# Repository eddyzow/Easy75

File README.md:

# Easy75

*because sometimes nine keys isn't enough...*

A custom 75% gasket-mounted mechanical keyboard run with a Raspberry Pi Pico. Features include 4.5-degree ergonomic incline, switch hotswap, 1.3" OLED screen, custom firmware, rotary encoder, custom printed circuit board (PCB), lubricated switches and stabilizers, and more! Created for Hack Club's Highway program.

[Easy75 Sound Test - Stock Akko V3 Creamy Blue Pro, Stock Durock V3](https://youtu.be/ZoHuPwVao3s)

# Gasket Mount

# PCB (designed and wired with KiCad)

# Case (designed in Onshape)

# Bill of Materials

| Item Name                                           | Purpose                                         | Item Source  | Quantity | Unit Cost (includes taxes) | Cost    | Notes                                                                 |
|:----------------------------------------------------|:------------------------------------------------|:-------------|---------:|:----------------------------|:--------|:----------------------------------------------------------------------|
| Akko V3 Creamy Blue Pro Switch (45pc)              | Mechanical switch for operating the keyboard    | Amazon       |        2 | $13.79                     | $27.58  |                                                                        |
| Pololu Laser-cut Switch Plate - 1.5mm Acrylic      | For switches to rest on and stability           | Pololu       |        1 | $31.00                     | $31.00  | Estimate -- precise cost is only available upon ordering               |
| 3D Printer Filament (PLA 1kg)                      | Print case (resin is too expensive)             | Bambu Lab    |        1 | $28.23                     | $28.23  |                                                                        |
| PCB x5 (min quantity)                              | Brains of the keyboard                          | JLCPCB       |        1 | $54.15                     | $54.15  | Could be $0 if PCBWay approves sponsorship                             |
| 1N4148 Diodes x100                                 | Prevents key ghosting                           | Amazon       |        1 | $5.73                      | $5.73   |                                                                        |
| Kailh Switch Sockets x50                           | Makes the board hotswap                         | Amazon       |        2 | $7.55                      | $15.10  |                                                                        |
| EC11 Rotary Encoder                                | Control for volume, etc in a knob               | AliExpress   |        1 | $6.11                      | $6.11   |                                                                        |
| Durock V3 Stabilizers                              | Stability for longer keys                       | Amazon       |        1 | $21.25                     | $21.25  |                                                                        |
| OLED Screen 128x64 1.3"                            | Provides a display for the keyboard             | Amazon       |        1 | $9.02                      | $9.02   |                                                                        |
| DIY Neoprene Gasket Strips                         | Creates a soft mount to improve sound quality   | Amazon       |        1 | $10.25                     | $10.25  |                                                                        |
| **TOTAL**                                          |                                                 |              |       12 |                            | **$225.66** |                                                                    |

For BOM with links, go to https://docs.google.com/spreadsheets/d/1KsEJJudN0m4QrFXq010_IyKu9P5RgScRp4gqEkQdcRI/edit?usp=sharing

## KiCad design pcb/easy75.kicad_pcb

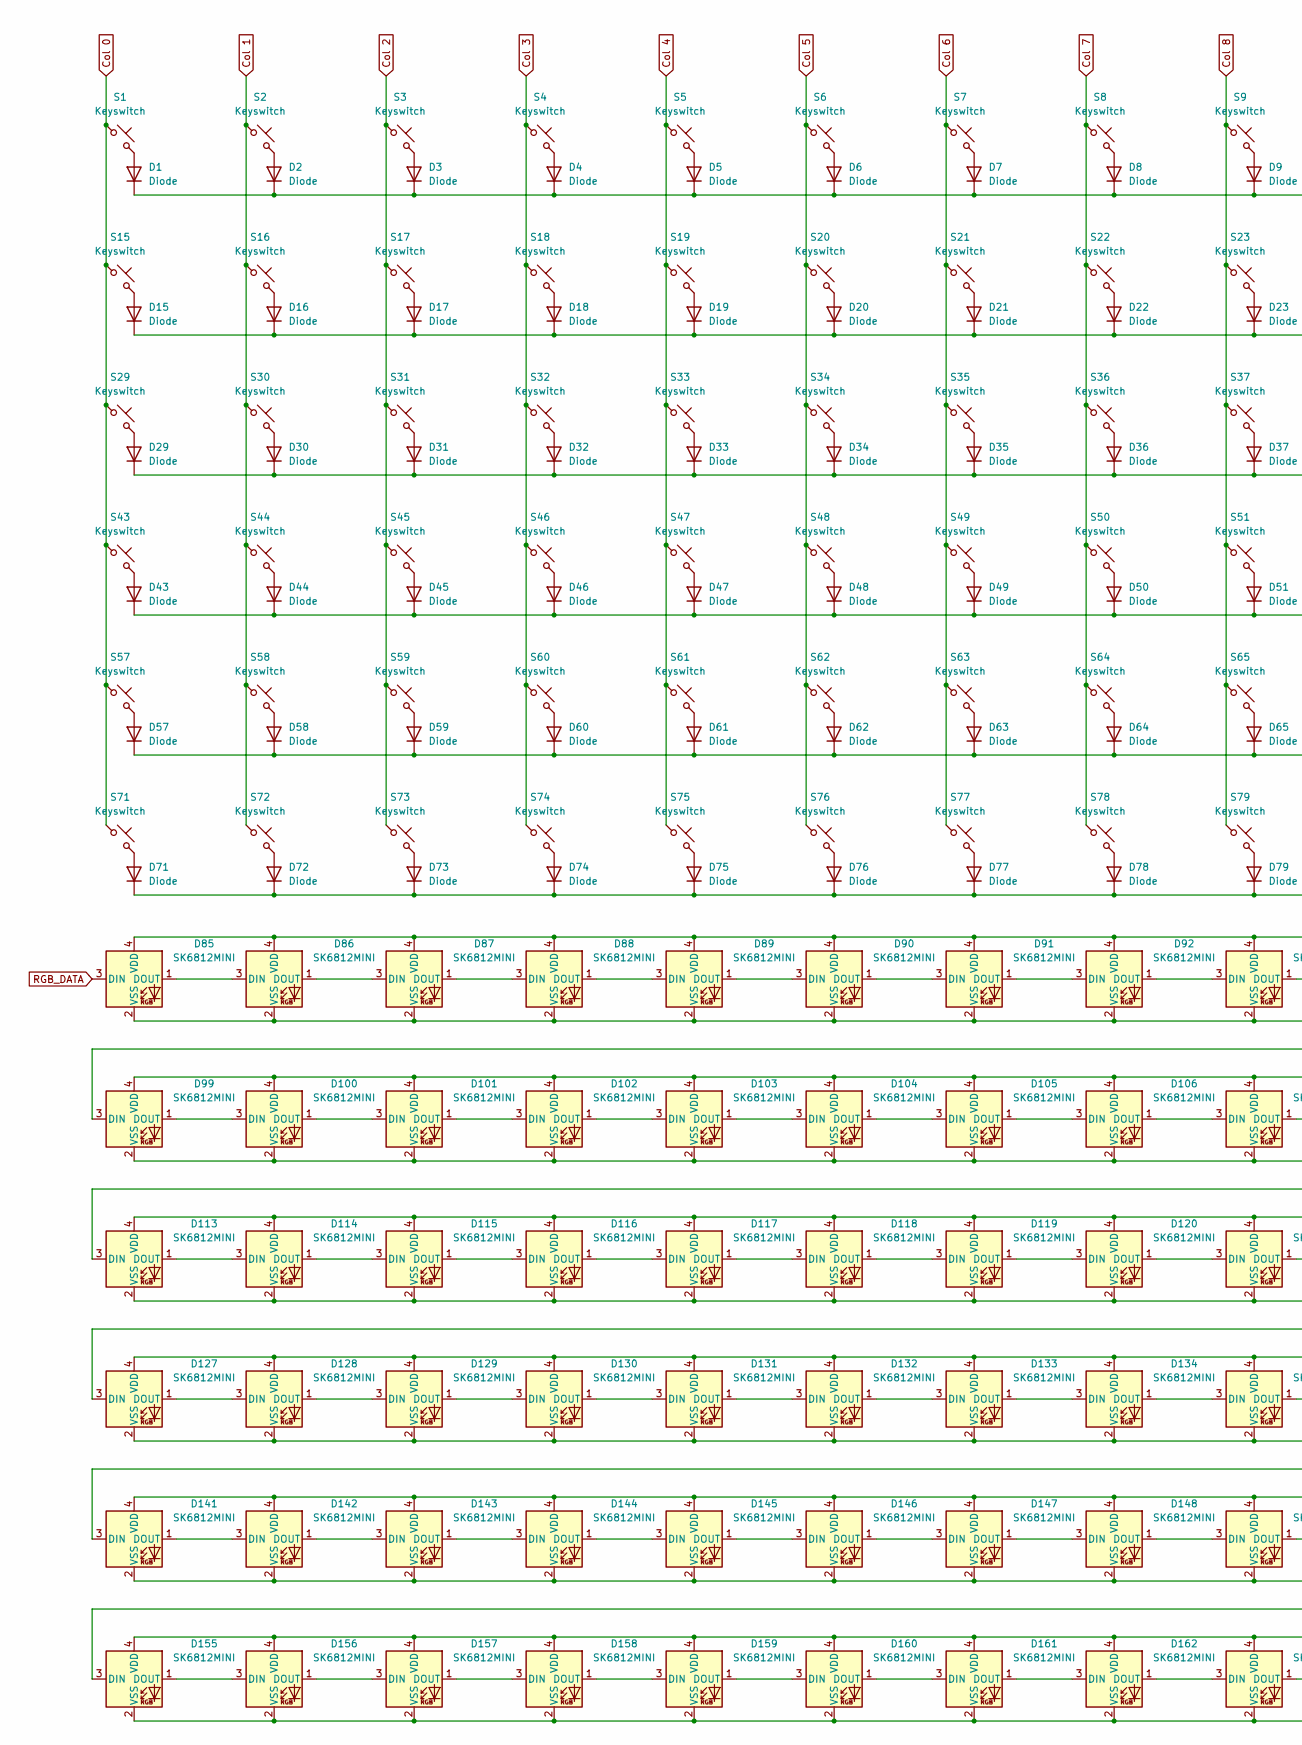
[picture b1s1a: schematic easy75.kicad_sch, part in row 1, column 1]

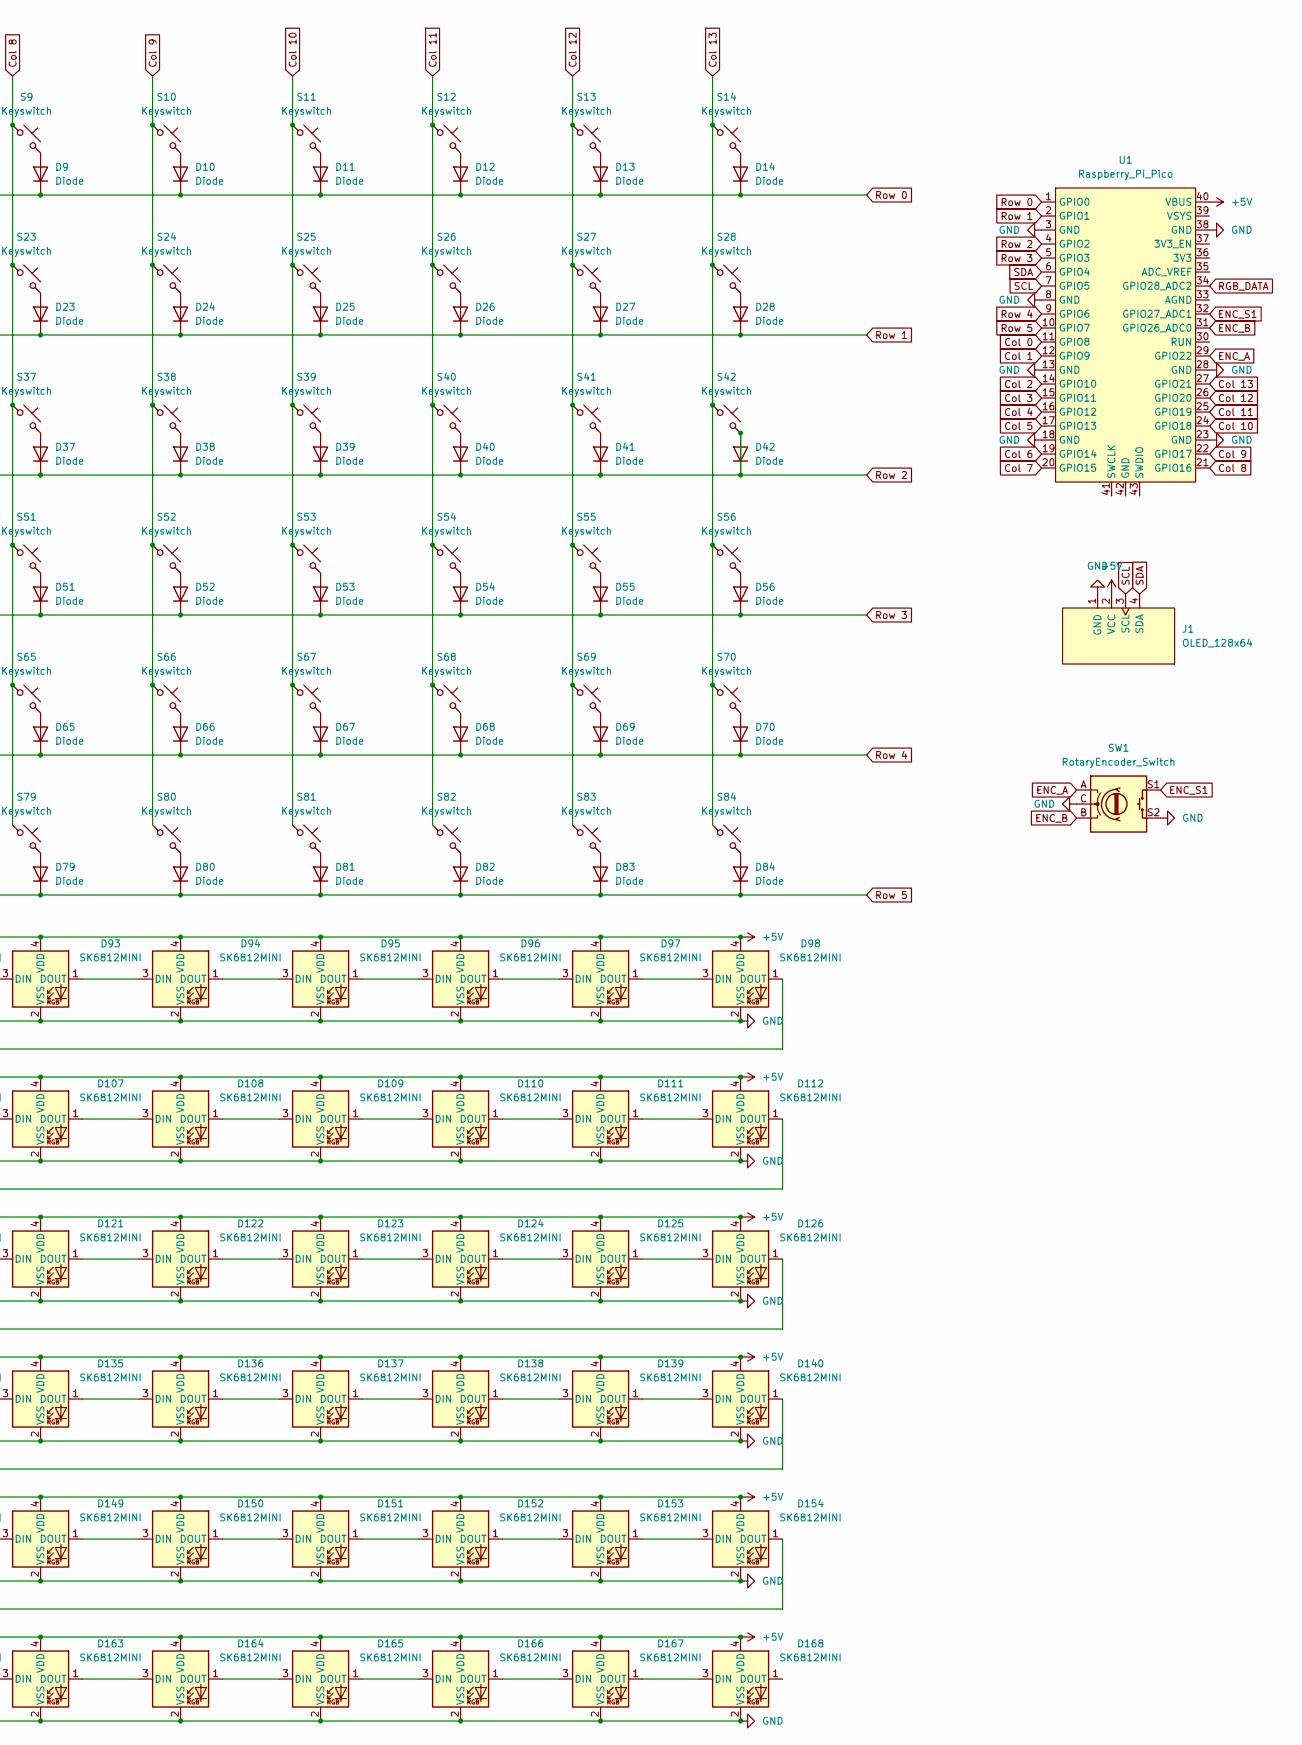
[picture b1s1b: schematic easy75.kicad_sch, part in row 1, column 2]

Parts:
D1, D2, D3, D4, D5, D6, D7, D8, D9, D10, D11, D12, D13, D14, D15, D16, D17, D18, D19, D20, D21, D22, D23, D24, D25, D26, D27, D28, D29, D30, D31, D32, D33, D34, D35, D36, D37, D38, D39, D40, D41, D42, D43, D44, D45, D46, D47, D48, D49, D50, D51, D52, D53, D54, D55, D56, D57, D58, D59, D60, D61, D62, D63, D64, D65, D66, D67, D68, D69, D70, D71, D72, D73, D74, D75, D76, D77, D78, D79, D80, D81, D82, D83, D84: Diode; Diode_DO-35
D85, D86, D87, D88, D89, D90, D91, D92, D93, D94, D95, D96, D97, D98, D99, D100, D101, D102, D103, D104, D105, D106, D107, D108, D109, D110, D111, D112, D113, D114, D115, D116, D117, D118, D119, D120, D121, D122, D123, D124, D125, D126, D127, D128, D129, D130, D131, D132, D133, D134, D135, D136, D137, D138, D139, D140, D141, D142, D143, D144, D145, D146, D147, D148, D149, D150, D151, D152, D153, D154, D155, D156, D157, D158, D159, D160, D161, D162, D163, D164, D165, D166, D167, D168: SK6812MINI; LED_SK6812MINI
J1: OLED_128x64
S1, S2, S3, S4, S5, S6, S7, S8, S9, S10, S11, S12, S13, S14, S15, S16, S17, S18, S19, S20, S21, S22, S23, S24, S25, S26, S27, S30, S31, S32, S33, S34, S35, S36, S37, S38, S39, S40, S41, S44, S45, S46, S47, S48, S49, S50, S51, S52, S53, S54, S57, S58, S59, S60, S61, S62, S63, S64, S65, S66, S68, S73, S74, S75, S76, S77, S78, S79, S80, S81, S82, S83, S84: Keyswitch; Hotswap_MX_1.00u
S28: Keyswitch; SW_Cherry_MX_2.00u_PCB
S29, S42: Keyswitch; Hotswap_MX_1.50u
S43, S67: Keyswitch; Hotswap_MX_1.75u
S55, S56: Keyswitch; SW_Cherry_MX_2.25u_PCB
S69, S70, S71: Keyswitch; Hotswap_MX_1.25u
S72: Keyswitch; Hotswap_MX_6.25u
SW1: RotaryEncoder_Switch; Encoder_EC11_MX
U1: Raspberry_Pi_Pico

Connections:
+5V: D85.4 (VDD), D86.4 (VDD), D87.4 (VDD), D88.4 (VDD), D89.4 (VDD), D90.4 (VDD), D91.4 (VDD), D92.4 (VDD), D93.4 (VDD), D94.4 (VDD), D95.4 (VDD), D96.4 (VDD), D97.4 (VDD), D98.4 (VDD), D99.4 (VDD), D100.4 (VDD), D101.4 (VDD), D102.4 (VDD), D103.4 (VDD), D104.4 (VDD), D105.4 (VDD), D106.4 (VDD), D107.4 (VDD), D108.4 (VDD), D109.4 (VDD), D110.4 (VDD), D111.4 (VDD), D112.4 (VDD), D113.4 (VDD), D114.4 (VDD), D115.4 (VDD), D116.4 (VDD), D117.4 (VDD), D118.4 (VDD), D119.4 (VDD), D120.4 (VDD), D121.4 (VDD), D122.4 (VDD), D123.4 (VDD), D124.4 (VDD), D125.4 (VDD), D126.4 (VDD), D127.4 (VDD), D128.4 (VDD), D129.4 (VDD), D130.4 (VDD), D131.4 (VDD), D132.4 (VDD), D133.4 (VDD), D134.4 (VDD), D135.4 (VDD), D136.4 (VDD), D137.4 (VDD), D138.4 (VDD), D139.4 (VDD), D140.4 (VDD), D141.4 (VDD), D142.4 (VDD), D143.4 (VDD), D144.4 (VDD), D145.4 (VDD), D146.4 (VDD), D147.4 (VDD), D148.4 (VDD), D149.4 (VDD), D150.4 (VDD), D151.4 (VDD), D152.4 (VDD), D153.4 (VDD), D154.4 (VDD), D155.4 (VDD), D156.4 (VDD), D157.4 (VDD), D158.4 (VDD), D159.4 (VDD), D160.4 (VDD), D161.4 (VDD), D162.4 (VDD), D163.4 (VDD), D164.4 (VDD), D165.4 (VDD), D166.4 (VDD), D167.4 (VDD), D168.4 (VDD), J1.2 (VCC), U1.40 (VBUS)
Col 0: S1.1, S15.1, S29.1, S43.1, S57.1, S71.1, U1.11 (GPIO8)
Col 1: S2.1, S16.1, S30.1, S44.1, S58.1, S72.1, U1.12 (GPIO9)
Col 2: S3.1, S17.1, S31.1, S45.1, S59.1, S73.1, U1.14 (GPIO10)
Col 3: S4.1, S18.1, S32.1, S46.1, S60.1, S74.1, U1.15 (GPIO11)
Col 4: S5.1, S19.1, S33.1, S47.1, S61.1, S75.1, U1.16 (GPIO12)
Col 5: S6.1, S20.1, S34.1, S48.1, S62.1, S76.1, U1.17 (GPIO13)
Col 6: S7.1, S21.1, S35.1, S49.1, S63.1, S77.1, U1.19 (GPIO14)
Col 7: S8.1, S22.1, S36.1, S50.1, S64.1, S78.1, U1.20 (GPIO15)
Col 8: S9.1, S23.1, S37.1, S51.1, S65.1, S79.1, U1.21 (GPIO16)
Col 9: S10.1, S24.1, S38.1, S52.1, S66.1, S80.1, U1.22 (GPIO17)
Col 10: S11.1, S25.1, S39.1, S53.1, S67.1, S81.1, U1.24 (GPIO18)
Col 11: S12.1, S26.1, S40.1, S54.1, S68.1, S82.1, U1.25 (GPIO19)
Col 12: S13.1, S27.1, S41.1, S55.1, S69.1, S83.1, U1.26 (GPIO20)
Col 13: S14.1, S28.1, S42.1, S56.1, S70.1, S84.1, U1.27 (GPIO21)
ENC_A: SW1.A, U1.29 (GPIO22)
ENC_B: SW1.B, U1.31 (GPIO26_ADC0)
ENC_S1: SW1.S1, U1.32 (GPIO27_ADC1)
GND: D85.2 (VSS), D86.2 (VSS), D87.2 (VSS), D88.2 (VSS), D89.2 (VSS), D90.2 (VSS), D91.2 (VSS), D92.2 (VSS), D93.2 (VSS), D94.2 (VSS), D95.2 (VSS), D96.2 (VSS), D97.2 (VSS), D98.2 (VSS), D99.2 (VSS), D100.2 (VSS), D101.2 (VSS), D102.2 (VSS), D103.2 (VSS), D104.2 (VSS), D105.2 (VSS), D106.2 (VSS), D107.2 (VSS), D108.2 (VSS), D109.2 (VSS), D110.2 (VSS), D111.2 (VSS), D112.2 (VSS), D113.2 (VSS), D114.2 (VSS), D115.2 (VSS), D116.2 (VSS), D117.2 (VSS), D118.2 (VSS), D119.2 (VSS), D120.2 (VSS), D121.2 (VSS), D122.2 (VSS), D123.2 (VSS), D124.2 (VSS), D125.2 (VSS), D126.2 (VSS), D127.2 (VSS), D128.2 (VSS), D129.2 (VSS), D130.2 (VSS), D131.2 (VSS), D132.2 (VSS), D133.2 (VSS), D134.2 (VSS), D135.2 (VSS), D136.2 (VSS), D137.2 (VSS), D138.2 (VSS), D139.2 (VSS), D140.2 (VSS), D141.2 (VSS), D142.2 (VSS), D143.2 (VSS), D144.2 (VSS), D145.2 (VSS), D146.2 (VSS), D147.2 (VSS), D148.2 (VSS), D149.2 (VSS), D150.2 (VSS), D151.2 (VSS), D152.2 (VSS), D153.2 (VSS), D154.2 (VSS), D155.2 (VSS), D156.2 (VSS), D157.2 (VSS), D158.2 (VSS), D159.2 (VSS), D160.2 (VSS), D161.2 (VSS), D162.2 (VSS), D163.2 (VSS), D164.2 (VSS), D165.2 (VSS), D166.2 (VSS), D167.2 (VSS), D168.2 (VSS), J1.1 (GND), SW1.C, SW1.S2, U1.3 (GND), U1.8 (GND), U1.13 (GND), U1.18 (GND), U1.23 (GND), U1.28 (GND), U1.38 (GND)
unnamed: D1.2 (A), S1.2
unnamed: D2.2 (A), S2.2
unnamed: D3.2 (A), S3.2
unnamed: D4.2 (A), S4.2
unnamed: D5.2 (A), S5.2
unnamed: D6.2 (A), S6.2
unnamed: D7.2 (A), S7.2
unnamed: D8.2 (A), S8.2
unnamed: D9.2 (A), S9.2
unnamed: D10.2 (A), S10.2
unnamed: D11.2 (A), S11.2
unnamed: D12.2 (A), S12.2
unnamed: D13.2 (A), S13.2
unnamed: D14.2 (A), S14.2
unnamed: D15.2 (A), S15.2
unnamed: D16.2 (A), S16.2
unnamed: D17.2 (A), S17.2
unnamed: D18.2 (A), S18.2
unnamed: D19.2 (A), S19.2
unnamed: D20.2 (A), S20.2
unnamed: D21.2 (A), S21.2
unnamed: D22.2 (A), S22.2
unnamed: D23.2 (A), S23.2
unnamed: D24.2 (A), S24.2
unnamed: D25.2 (A), S25.2
unnamed: D26.2 (A), S26.2
unnamed: D27.2 (A), S27.2
unnamed: D28.2 (A), S28.2
unnamed: D29.2 (A), S29.2
unnamed: D30.2 (A), S30.2
unnamed: D31.2 (A), S31.2
unnamed: D32.2 (A), S32.2
unnamed: D33.2 (A), S33.2
unnamed: D34.2 (A), S34.2
unnamed: D35.2 (A), S35.2
unnamed: D36.2 (A), S36.2
unnamed: D37.2 (A), S37.2
unnamed: D38.2 (A), S38.2
unnamed: D39.2 (A), S39.2
unnamed: D40.2 (A), S40.2
unnamed: D41.2 (A), S41.2
unnamed: D43.2 (A), S43.2
unnamed: D44.2 (A), S44.2
unnamed: D45.2 (A), S45.2
unnamed: D46.2 (A), S46.2
unnamed: D47.2 (A), S47.2
unnamed: D48.2 (A), S48.2
unnamed: D49.2 (A), S49.2
unnamed: D50.2 (A), S50.2
unnamed: D51.2 (A), S51.2
unnamed: D52.2 (A), S52.2
unnamed: D53.2 (A), S53.2
unnamed: D54.2 (A), S54.2
unnamed: D55.2 (A), S55.2
unnamed: D56.2 (A), S56.2
unnamed: D57.2 (A), S57.2
unnamed: D58.2 (A), S58.2
unnamed: D59.2 (A), S59.2
unnamed: D60.2 (A), S60.2
unnamed: D61.2 (A), S61.2
unnamed: D62.2 (A), S62.2
unnamed: D63.2 (A), S63.2
unnamed: D64.2 (A), S64.2
unnamed: D65.2 (A), S65.2
unnamed: D66.2 (A), S66.2
unnamed: D67.2 (A), S67.2
unnamed: D68.2 (A), S68.2
unnamed: D69.2 (A), S69.2
unnamed: D70.2 (A), S70.2
unnamed: D71.2 (A), S71.2
unnamed: D72.2 (A), S72.2
unnamed: D73.2 (A), S73.2
unnamed: D74.2 (A), S74.2
unnamed: D75.2 (A), S75.2
unnamed: D76.2 (A), S76.2
unnamed: D77.2 (A), S77.2
unnamed: D78.2 (A), S78.2
unnamed: D79.2 (A), S79.2
unnamed: D80.2 (A), S80.2
unnamed: D81.2 (A), S81.2
unnamed: D82.2 (A), S82.2
unnamed: D83.2 (A), S83.2
unnamed: D84.2 (A), S84.2
unnamed: D85.1 (DOUT), D86.3 (DIN)
unnamed: D86.1 (DOUT), D87.3 (DIN)
unnamed: D87.1 (DOUT), D88.3 (DIN)
unnamed: D88.1 (DOUT), D89.3 (DIN)
unnamed: D89.1 (DOUT), D90.3 (DIN)
unnamed: D90.1 (DOUT), D91.3 (DIN)
unnamed: D91.1 (DOUT), D92.3 (DIN)
unnamed: D92.1 (DOUT), D93.3 (DIN)
unnamed: D93.1 (DOUT), D94.3 (DIN)
unnamed: D94.1 (DOUT), D95.3 (DIN)
unnamed: D95.1 (DOUT), D96.3 (DIN)
unnamed: D96.1 (DOUT), D97.3 (DIN)
unnamed: D97.1 (DOUT), D98.3 (DIN)
unnamed: D98.1 (DOUT), D99.3 (DIN)
unnamed: D99.1 (DOUT), D100.3 (DIN)
unnamed: D100.1 (DOUT), D101.3 (DIN)
unnamed: D101.1 (DOUT), D102.3 (DIN)
unnamed: D102.1 (DOUT), D103.3 (DIN)
unnamed: D103.1 (DOUT), D104.3 (DIN)
unnamed: D104.1 (DOUT), D105.3 (DIN)
unnamed: D105.1 (DOUT), D106.3 (DIN)
unnamed: D106.1 (DOUT), D107.3 (DIN)
unnamed: D107.1 (DOUT), D108.3 (DIN)
unnamed: D108.1 (DOUT), D109.3 (DIN)
unnamed: D109.1 (DOUT), D110.3 (DIN)
unnamed: D110.1 (DOUT), D111.3 (DIN)
unnamed: D111.1 (DOUT), D112.3 (DIN)
unnamed: D112.1 (DOUT), D113.3 (DIN)
unnamed: D113.1 (DOUT), D114.3 (DIN)
unnamed: D114.1 (DOUT), D115.3 (DIN)
unnamed: D115.1 (DOUT), D116.3 (DIN)
unnamed: D116.1 (DOUT), D117.3 (DIN)
unnamed: D117.1 (DOUT), D118.3 (DIN)
unnamed: D118.1 (DOUT), D119.3 (DIN)
unnamed: D119.1 (DOUT), D120.3 (DIN)
unnamed: D120.1 (DOUT), D121.3 (DIN)
unnamed: D121.1 (DOUT), D122.3 (DIN)
unnamed: D122.1 (DOUT), D123.3 (DIN)
unnamed: D123.1 (DOUT), D124.3 (DIN)
unnamed: D124.1 (DOUT), D125.3 (DIN)
unnamed: D125.1 (DOUT), D126.3 (DIN)
unnamed: D126.1 (DOUT), D127.3 (DIN)
unnamed: D127.1 (DOUT), D128.3 (DIN)
unnamed: D128.1 (DOUT), D129.3 (DIN)
unnamed: D129.1 (DOUT), D130.3 (DIN)
unnamed: D130.1 (DOUT), D131.3 (DIN)
unnamed: D131.1 (DOUT), D132.3 (DIN)
unnamed: D132.1 (DOUT), D133.3 (DIN)
unnamed: D133.1 (DOUT), D134.3 (DIN)
unnamed: D134.1 (DOUT), D135.3 (DIN)
unnamed: D135.1 (DOUT), D136.3 (DIN)
unnamed: D136.1 (DOUT), D137.3 (DIN)
unnamed: D137.1 (DOUT), D138.3 (DIN)
unnamed: D138.1 (DOUT), D139.3 (DIN)
unnamed: D139.1 (DOUT), D140.3 (DIN)
unnamed: D140.1 (DOUT), D141.3 (DIN)
unnamed: D141.1 (DOUT), D142.3 (DIN)
unnamed: D142.1 (DOUT), D143.3 (DIN)
unnamed: D143.1 (DOUT), D144.3 (DIN)
unnamed: D144.1 (DOUT), D145.3 (DIN)
unnamed: D145.1 (DOUT), D146.3 (DIN)
unnamed: D146.1 (DOUT), D147.3 (DIN)
unnamed: D147.1 (DOUT), D148.3 (DIN)
unnamed: D148.1 (DOUT), D149.3 (DIN)
unnamed: D149.1 (DOUT), D150.3 (DIN)
unnamed: D150.1 (DOUT), D151.3 (DIN)
unnamed: D151.1 (DOUT), D152.3 (DIN)
unnamed: D152.1 (DOUT), D153.3 (DIN)
unnamed: D153.1 (DOUT), D154.3 (DIN)
unnamed: D154.1 (DOUT), D155.3 (DIN)
unnamed: D155.1 (DOUT), D156.3 (DIN)
unnamed: D156.1 (DOUT), D157.3 (DIN)
unnamed: D157.1 (DOUT), D158.3 (DIN)
unnamed: D158.1 (DOUT), D159.3 (DIN)
unnamed: D159.1 (DOUT), D160.3 (DIN)
unnamed: D160.1 (DOUT), D161.3 (DIN)
unnamed: D161.1 (DOUT), D162.3 (DIN)
unnamed: D162.1 (DOUT), D163.3 (DIN)
unnamed: D163.1 (DOUT), D164.3 (DIN)
unnamed: D164.1 (DOUT), D165.3 (DIN)
unnamed: D165.1 (DOUT), D166.3 (DIN)
unnamed: D166.1 (DOUT), D167.3 (DIN)
unnamed: D167.1 (DOUT), D168.3 (DIN)
RGB_DATA: D85.3 (DIN), U1.34 (GPIO28_ADC2)
Row 0: D1.1 (K), D2.1 (K), D3.1 (K), D4.1 (K), D5.1 (K), D6.1 (K), D7.1 (K), D8.1 (K), D9.1 (K), D10.1 (K), D11.1 (K), D12.1 (K), D13.1 (K), D14.1 (K), U1.1 (GPIO0)
Row 1: D15.1 (K), D16.1 (K), D17.1 (K), D18.1 (K), D19.1 (K), D20.1 (K), D21.1 (K), D22.1 (K), D23.1 (K), D24.1 (K), D25.1 (K), D26.1 (K), D27.1 (K), D28.1 (K), U1.2 (GPIO1)
Row 2: D29.1 (K), D30.1 (K), D31.1 (K), D32.1 (K), D33.1 (K), D34.1 (K), D35.1 (K), D36.1 (K), D37.1 (K), D38.1 (K), D39.1 (K), D40.1 (K), D41.1 (K), D42.1 (K), D42.2 (A), S42.2, U1.4 (GPIO2)
Row 3: D43.1 (K), D44.1 (K), D45.1 (K), D46.1 (K), D47.1 (K), D48.1 (K), D49.1 (K), D50.1 (K), D51.1 (K), D52.1 (K), D53.1 (K), D54.1 (K), D55.1 (K), D56.1 (K), U1.5 (GPIO3)
Row 4: D57.1 (K), D58.1 (K), D59.1 (K), D60.1 (K), D61.1 (K), D62.1 (K), D63.1 (K), D64.1 (K), D65.1 (K), D66.1 (K), D67.1 (K), D68.1 (K), D69.1 (K), D70.1 (K), U1.9 (GPIO6)
Row 5: D71.1 (K), D72.1 (K), D73.1 (K), D74.1 (K), D75.1 (K), D76.1 (K), D77.1 (K), D78.1 (K), D79.1 (K), D80.1 (K), D81.1 (K), D82.1 (K), D83.1 (K), D84.1 (K), U1.10 (GPIO7)
SCL: J1.3 (SCL), U1.7 (GPIO5)
SDA: J1.4 (SDA), U1.6 (GPIO4)

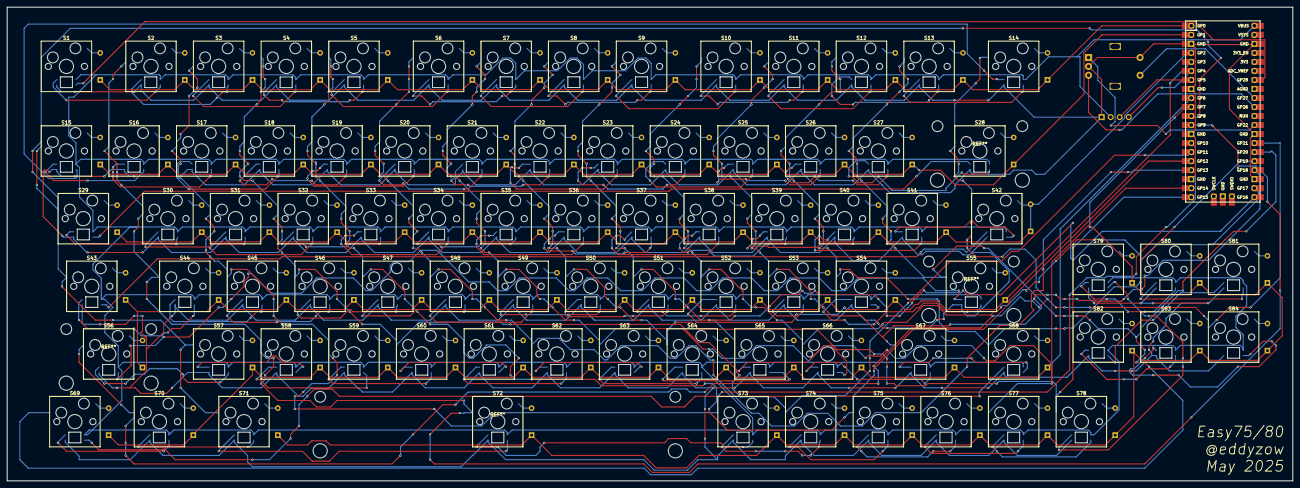
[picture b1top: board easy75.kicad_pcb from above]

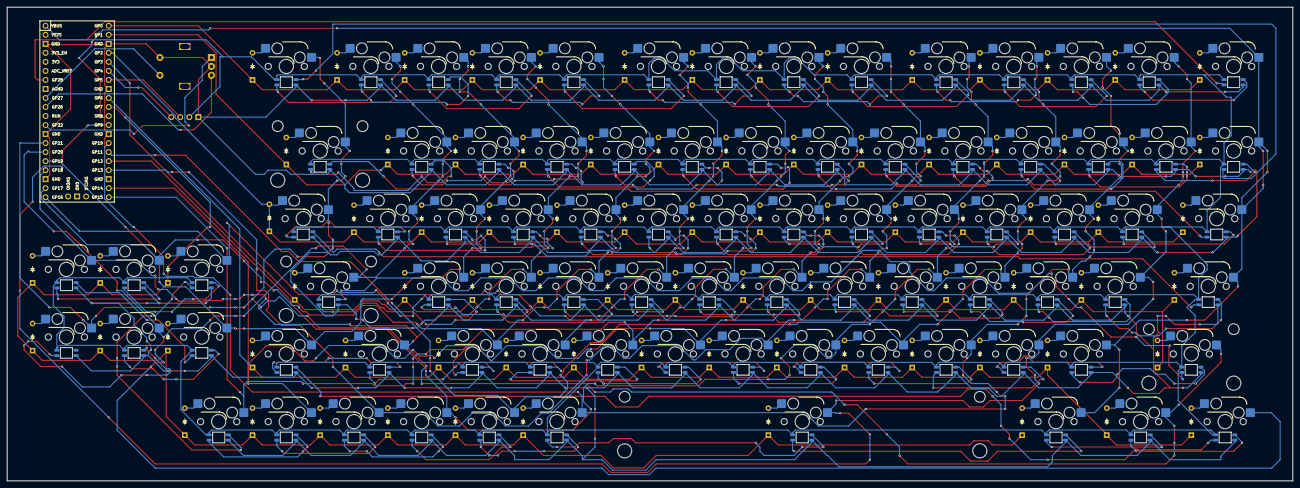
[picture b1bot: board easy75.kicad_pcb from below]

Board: 2 copper layers, 361.9 x 133.3 mm, 255 parts (168 on the bottom side), 194 nets.
